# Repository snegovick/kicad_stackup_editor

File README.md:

# Description

Stackup editor helps to create stackup diagram for KiCAD PCBs. 
Stackup diagram may be required for some PCB factories. 

## Do I need this ?

Popular PCB factories usually already have stackup editor embedded into their online order forms,
so there is no need for separate diagram. 
Others will explicitly ask you about stackup. 
Even then you can just describe stackup in textual form. 
This program is just for unification and convenience.

# Install

## Ubuntu 18.10

Ubuntu 18.10 already has all prerequisites installed, just run the script

## Running from source

This program requires python3, gtk3, cairo, pango.
Install prerequisites and run **kicad-stackup-editor**.

## Building deb package for your system

This repository contains Makefile which can be used to build *deb* package.

To build package run:

```
make deb
```

Package building script requires python3-stdeb, lsb_release, debuild, git.
To install these packages run:

```
# apt-get install python3-stdeb lsb-release devscripts git
```

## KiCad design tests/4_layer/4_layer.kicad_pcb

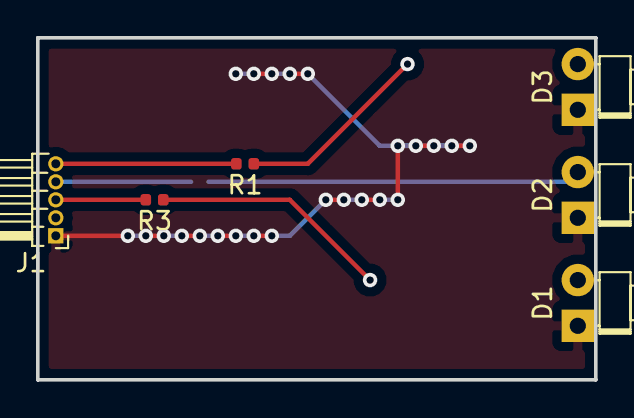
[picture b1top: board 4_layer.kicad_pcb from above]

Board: 4 copper layers, 31.0 x 19.0 mm, 7 parts (1 on the bottom side), 7 nets.

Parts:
D1, D2, D3: LED; LED_D1.8mm_W1.8mm_H2.4mm_Horizontal_O1.27mm_Z1.6mm
J1: Conn_01x05_Female; PinHeader_1x05_P1.00mm_Horizontal
R1, R2, R3: R_Small; R_0402_1005Metric

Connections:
Earth: D1.1, D2.1, D3.1, J1.1
unnamed: D1.2, R3.1
unnamed: D2.2, R2.1
unnamed: D3.2, R1.1
unnamed: J1.3, R3.2
unnamed: J1.4, R2.2
unnamed: J1.5, R1.2

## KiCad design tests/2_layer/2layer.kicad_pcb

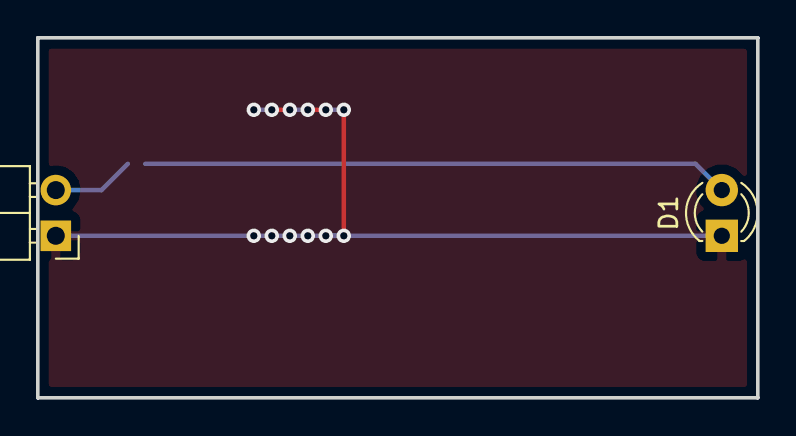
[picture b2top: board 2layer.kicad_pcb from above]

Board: 2 copper layers, 40.0 x 20.0 mm, 3 parts (1 on the bottom side), 3 nets.

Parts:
D1: LED; LED_D3.0mm
J1: Conn_01x02_Female; PinHeader_1x02_P2.54mm_Horizontal
R1: R_Small; R_0402_1005Metric

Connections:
+5V: J1.2, R1.1
Earth: D1.1, J1.1
unnamed: D1.2, R1.2

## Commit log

2019-01-24 Initial
2019-01-26 Added python and debian packaging meta-data Issues: #4, #5
2019-01-26 Fixed dirty working directory error message; Updated deps for python3
2019-01-26 Removed package info from setup.py #4
2019-01-26 Added prebuilt setup.py #4 Updated install info in README #6
2020-03-06 added cli option for output generation
2020-03-10 Issue #8: Add command-line argument output for headless stackup generation with default params
